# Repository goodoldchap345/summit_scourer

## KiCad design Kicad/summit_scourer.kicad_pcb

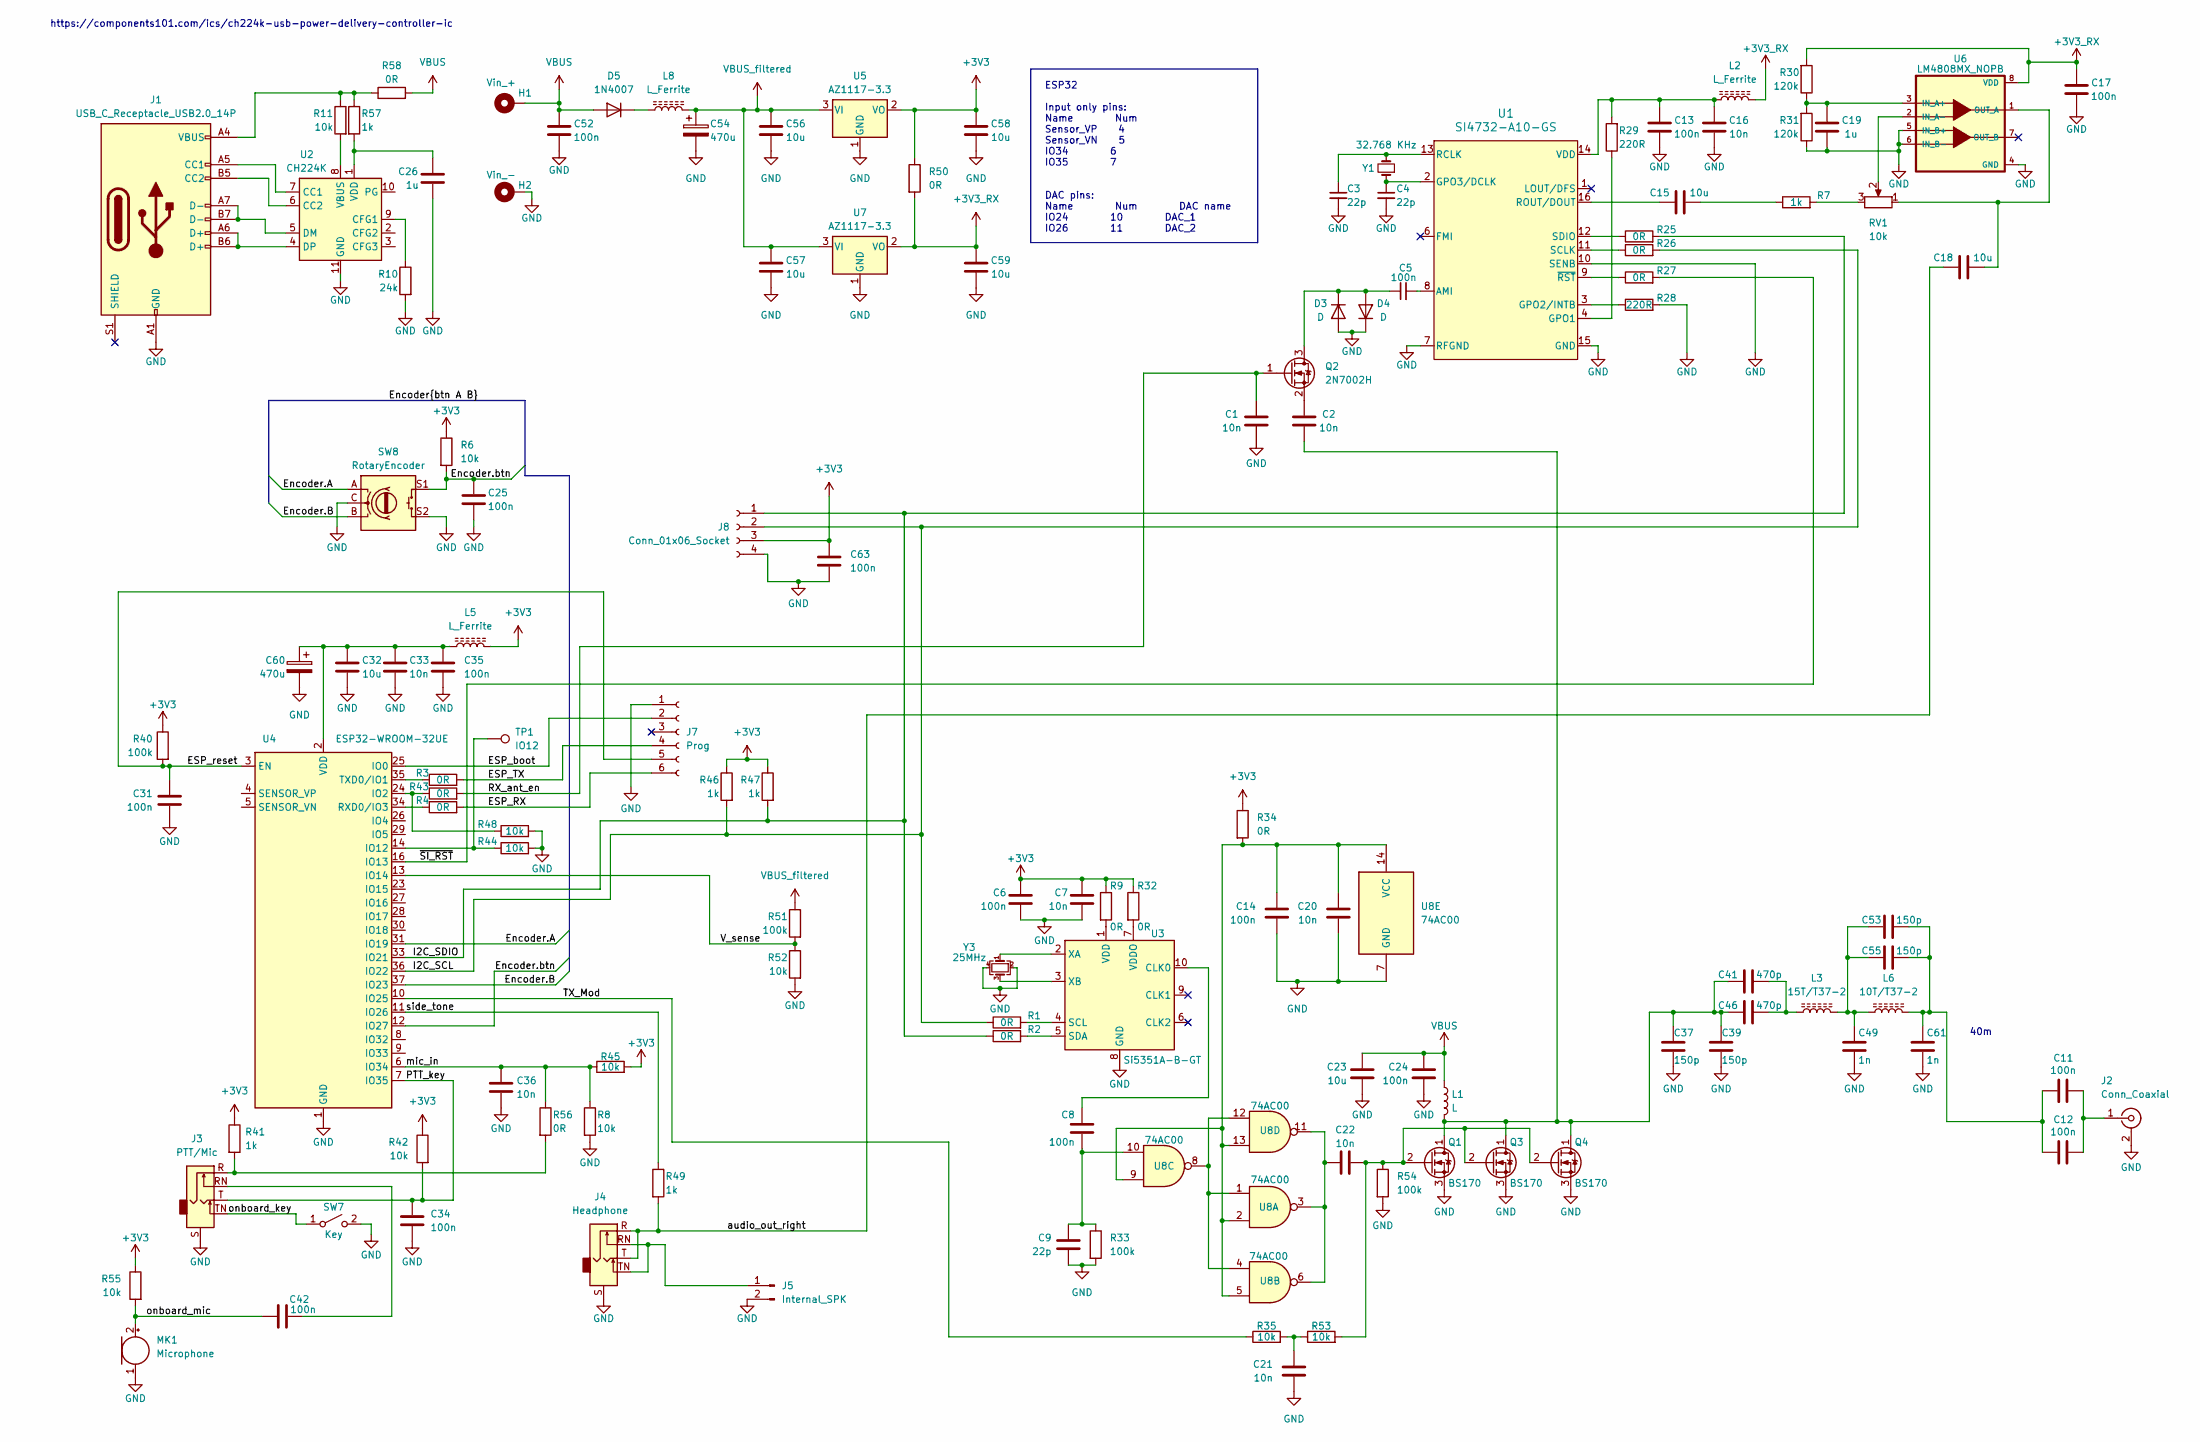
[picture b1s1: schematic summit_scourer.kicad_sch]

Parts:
C1, C2, C7, C16, C20, C21, C22, C33, C36: 10n; C_0603_1608Metric_Pad1.08x0.95mm_HandSolder
C3, C4, C9: 22p; C_0603_1608Metric_Pad1.08x0.95mm_HandSolder
C5, C6, C8, C11, C12, C13, C14, C17, C24, C25, C31, C34, C35, C42, C52, C63: 100n; C_0603_1608Metric_Pad1.08x0.95mm_HandSolder
C15, C18, C32, C56, C57, C58, C59: 10u; C_1210_3225Metric_Pad1.33x2.70mm_HandSolder
C19, C26: 1u; C_0603_1608Metric_Pad1.08x0.95mm_HandSolder
C23: 10u; C_1210_3225Metric
C37, C39, C53, C55: 150p; C_0603_1608Metric_Pad1.08x0.95mm_HandSolder
C41, C46: 470p; C_0603_1608Metric_Pad1.08x0.95mm_HandSolder
C49, C61: 1n; C_0603_1608Metric_Pad1.08x0.95mm_HandSolder
C54, C60: 470u; CP_Radial_D8.0mm_P3.80mm
D3, D4: D; D_PowerDI-123
D5: 1N4007; D_A-405_P2.54mm_Vertical_AnodeUp
H1: Vin_+; TestPoint_THTPad_3.0x3.0mm_Drill1.5mm
H2: Vin_-; TestPoint_THTPad_3.0x3.0mm_Drill1.5mm
J1: USB_C_Receptacle_USB2.0_14P; USB-C Korean_HROPart
J2: Conn_Coaxial; SMA_Amphenol_901-143_Horizontal
J3: PTT/Mic; Jack_3.5mm_CUI_SJ1-3525N_Horizontal
J4: Headphone; Jack_3.5mm_CUI_SJ1-3525N_Horizontal
J5: Internal_SPK; PinHeader_1x02_P2.54mm_Vertical
J7: Prog; PinHeader_1x06_P2.54mm_Vertical
J8: Conn_01x06_Socket; PinHeader_1x04_P2.54mm_Vertical
L1: L; L_Toroid_Vertical_L10.0mm_W5.0mm_P5.08mm
L2, L5: L_Ferrite; L_TDK_SLF6025
L3: 15T/T37-2; L_Toroid_Vertical_L10.0mm_W5.0mm_P5.08mm
L6: 10T/T37-2; L_Toroid_Vertical_L10.0mm_W5.0mm_P5.08mm
L8: L_Ferrite; L_6.3x6.3_H3
MK1: Microphone; PinHeader_1x02_P2.54mm_Vertical
Q1, Q3, Q4: BS170; TO-92_Inline
Q2: 2N7002H; SOT-23
R1, R2, R3, R4, R9, R25, R26, R27, R32, R34, R43, R50, R56, R58: 0R; R_0603_linked
R6, R8, R11, R35, R42, R44, R45, R48, R52, R53, R55: 10k; R_0603_1608Metric
R7, R41, R46, R47, R49, R57: 1k; R_0603_1608Metric
R10: 24k; R_0603_1608Metric
R28, R29: 220R; R_0603_1608Metric
R30, R31: 120k; R_0603_1608Metric
R33, R40, R51, R54: 100k; R_0603_1608Metric
RV1: 10k; PinHeader_1x03_P2.54mm_Vertical
SW7: Key; PinHeader_1x02_P2.54mm_Vertical
SW8: RotaryEncoder; Rotary_encoder
TP1: IO12; PinHeader_1x01_P2.54mm_Vertical
U1: SI4732-A10-GS; SO-16_3.9x9.9mm_P1.27mm
U2: CH224K; SSOP-10-1EP_3.9x4.9mm_P1mm_EP2.1x3.3mm
U3: Si5351A-B-GT; MSOP-10_3x3mm_P0.5mm
U4: ESP32-WROOM-32UE
U5, U7: AZ1117-3.3; TO-252-2
U6: LM4808MX_NOPB; SO-8_3.9x4.9mm_P1.27mm
U8: 74AC00; SOIC-14_3.9x8.7mm_P1.27mm
Y1: 32.768 KHz; Crystal_SMD_3215-2Pin_3.2x1.5mm; Part Num ABS07AIG-32.768KHZ-D-T
Y3: 25MHz; Crystal_SMD_3225-4Pin_3.2x2.5mm

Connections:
+3V3: C6.1, C7.1, C58.1, C63.1, J8.3, L5.2, R6.1, R9.1, R32.1, R34.1, R40.1, R41.1, R42.1, R45.2, R46.1, R47.1, R50.1, R55.1, U5.2 (VO)
+3V3_RX: C17.1, C59.1, L2.2, R30.2, R50.2, U6.8 (VDD), U7.2 (VO)
/ESP_RX: J7.6, R4.2
/ESP_TX: J7.4, R3.2
/ESP_boot: J7.2, U4.25 (IO0)
/ESP_reset: C31.1, J7.5, R40.2, U4.3 (EN)
/Encoder.A: SW8.A, U4.31 (IO19)
/Encoder.B: SW8.B, U4.37 (IO23)
/Encoder.btn: C25.1, R6.2, SW8.S1, U4.12 (IO27)
/I2C_SCL: J8.2, R1.1, R26.2, R46.2, U4.36 (IO22)
/I2C_SDIO: J8.1, R2.1, R25.2, R47.2, U4.33 (IO21)
/PTT_key: C34.1, J3.T, R42.2, U4.7 (IO35)
/RX_ant_en: C1.1, Q2.1 (G), R43.2
/TX_Mod: R35.1, U4.10 (IO25)
/V_sense: R51.2, R52.1, U4.13 (IO14)
/audio_out_right: C18.1, J4.R, J4.T, R49.2
/mic_in: C36.1, R8.1, R45.1, R56.1, U4.6 (IO34)
/onboard_key: J3.TN, SW7.1 (A)
/onboard_mic: C42.1, MK1.2 (+), R55.2
/side_tone: R49.1, U4.11 (IO26)
/~SI_RST: R27.2, U4.16 (IO13)
GND: C1.2, C3.2, C4.2, C6.2, C7.2, C9.2, C13.2, C14.2, C16.2, C17.2, C19.2, C20.2, C21.2, C23.2, C24.2, C25.2, C26.2, C31.2, C32.2, C33.2, C34.2, C35.2, C36.2, C37.2, C39.2, C49.1, C52.2, C54.2, C56.2, C57.2, C58.2, C59.2, C60.2, C61.2, C63.2, D3.2 (A), D4.1 (K), H2.1, J1.A1 (GND), J1.A12 (GND), J1.B1 (GND), J1.B12 (GND), J2.2 (Ext), J3.S, J4.S, J5.2, J7.1, J8.4, MK1.1 (-), Q1.3 (S), Q3.3 (S), Q4.3 (S), R8.2, R10.2, R28.2, R31.1, R33.2, R44.2, R48.2, R52.2, R54.2, SW7.2 (B), SW8.C, SW8.S2, U1.7 (RFGND), U1.10 (SENB), U1.15 (GND), U2.11 (GND), U3.8 (GND), U4.1 (GND), U4.15 (GND), U4.38 (GND), U4.39 (GND), U5.1 (GND), U6.4 (GND), U6.5 (IN_B+), U6.6 (IN_B-), U7.1 (GND), U8.7 (GND), Y3.2, Y3.4
unnamed: C8.1, C9.1, R33.1, U8.10
unnamed: C11.1, C12.1, C53.2, C55.2, C61.1, L6.2
unnamed: C15.2, R7.1
unnamed: C21.1, R35.2, R53.1
unnamed: C22.1, U8.3, U8.6, U8.11
unnamed: C41.2, C46.2, L3.1
unnamed: C42.2, J3.RN
unnamed: C49.2, C53.1, C55.1, L3.2, L6.1
unnamed: C5.1, D3.1 (K), D4.2 (A), Q2.3 (D)
unnamed: D5.1 (K), L8.1
unnamed: J1.A5 (CC1), U2.7 (CC1)
unnamed: J1.B5 (CC2), U2.6 (CC2)
unnamed: J1.A4 (VBUS), J1.A9 (VBUS), J1.B4 (VBUS), J1.B9 (VBUS), R11.1, R57.1, R58.1
unnamed: C11.2, C12.2, J2.1 (In)
unnamed: J3.R, R41.2, R56.2
unnamed: J4.RN, J4.TN, J5.1
unnamed: C2.2, C37.1, C39.1, C41.1, C46.1, L1.2, Q1.1 (D), Q3.1 (D), Q4.1 (D)
unnamed: C22.2, Q1.2 (G), Q3.2 (G), Q4.2 (G), R53.2, R54.1
unnamed: C2.1, Q2.2 (S)
unnamed: R7.2, RV1.3
unnamed: C5.2, U1.8 (AMI)
unnamed: R29.1, U1.4 (GPO1)
unnamed: R28.1, U1.3 (GPO2/INTB)
unnamed: C4.1, U1.2 (GPO3/DCLK), Y1.1
unnamed: C3.1, U1.13 (RCLK), Y1.2
unnamed: C15.1, U1.16 (ROUT/DOUT)
unnamed: R26.1, U1.11 (SCLK)
unnamed: R25.1, U1.12 (SDIO)
unnamed: C13.1, C16.1, L2.1, R29.2, U1.14 (VDD)
unnamed: R27.1, U1.9 (~RST)
unnamed: R10.1, U2.9 (CFG1)
unnamed: J1.A7 (D-), J1.B7 (D-), U2.5 (DM)
unnamed: J1.A6 (D+), J1.B6 (D+), U2.4 (DP)
unnamed: R11.2, U2.8 (VBUS)
unnamed: C26.1, R57.2, U2.1 (VDD)
unnamed: C8.2, U3.10 (CLK0)
unnamed: R1.2, U3.4 (SCL)
unnamed: R2.2, U3.5 (SDA)
unnamed: R9.2, U3.1 (VDD)
unnamed: R32.2, U3.7 (VDDO)
unnamed: U3.2 (XA), Y3.1
unnamed: U3.3 (XB), Y3.3
unnamed: R43.1, R48.1, U4.24 (IO2)
unnamed: R44.1, TP1.1, U4.14 (IO12)
unnamed: R4.1, U4.34 (RXD0/IO3)
unnamed: R3.1, U4.35 (TXD0/IO1)
unnamed: C32.1, C33.1, C35.1, C60.1, L5.1, U4.2 (VDD)
unnamed: C19.1, R30.1, R31.2, U6.3 (IN_A+)
unnamed: RV1.2, U6.2 (IN_A-)
unnamed: C18.2, RV1.1, U6.1 (OUT_A)
unnamed: U8.1, U8.4, U8.8, U8.12
unnamed: C14.1, C20.1, R34.2, U8.2, U8.5, U8.9, U8.13, U8.14 (VCC)
VBUS: C23.1, C24.1, C52.1, D5.2 (A), H1.1, L1.1, R58.2
VBUS_filtered: C54.1, C56.1, C57.1, L8.2, R51.1, U5.3 (VI), U7.3 (VI)

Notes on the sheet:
ESP32 Input only pins: Name Num Sensor_VP 4 Sensor_VN 5 IO34 6 IO35 7 DAC pins: Name Num DAC name IO24 10 DAC_1 IO26 11 DAC_2
https://components101.com/ics/ch224k-usb-power-delivery-controller-ic
40m

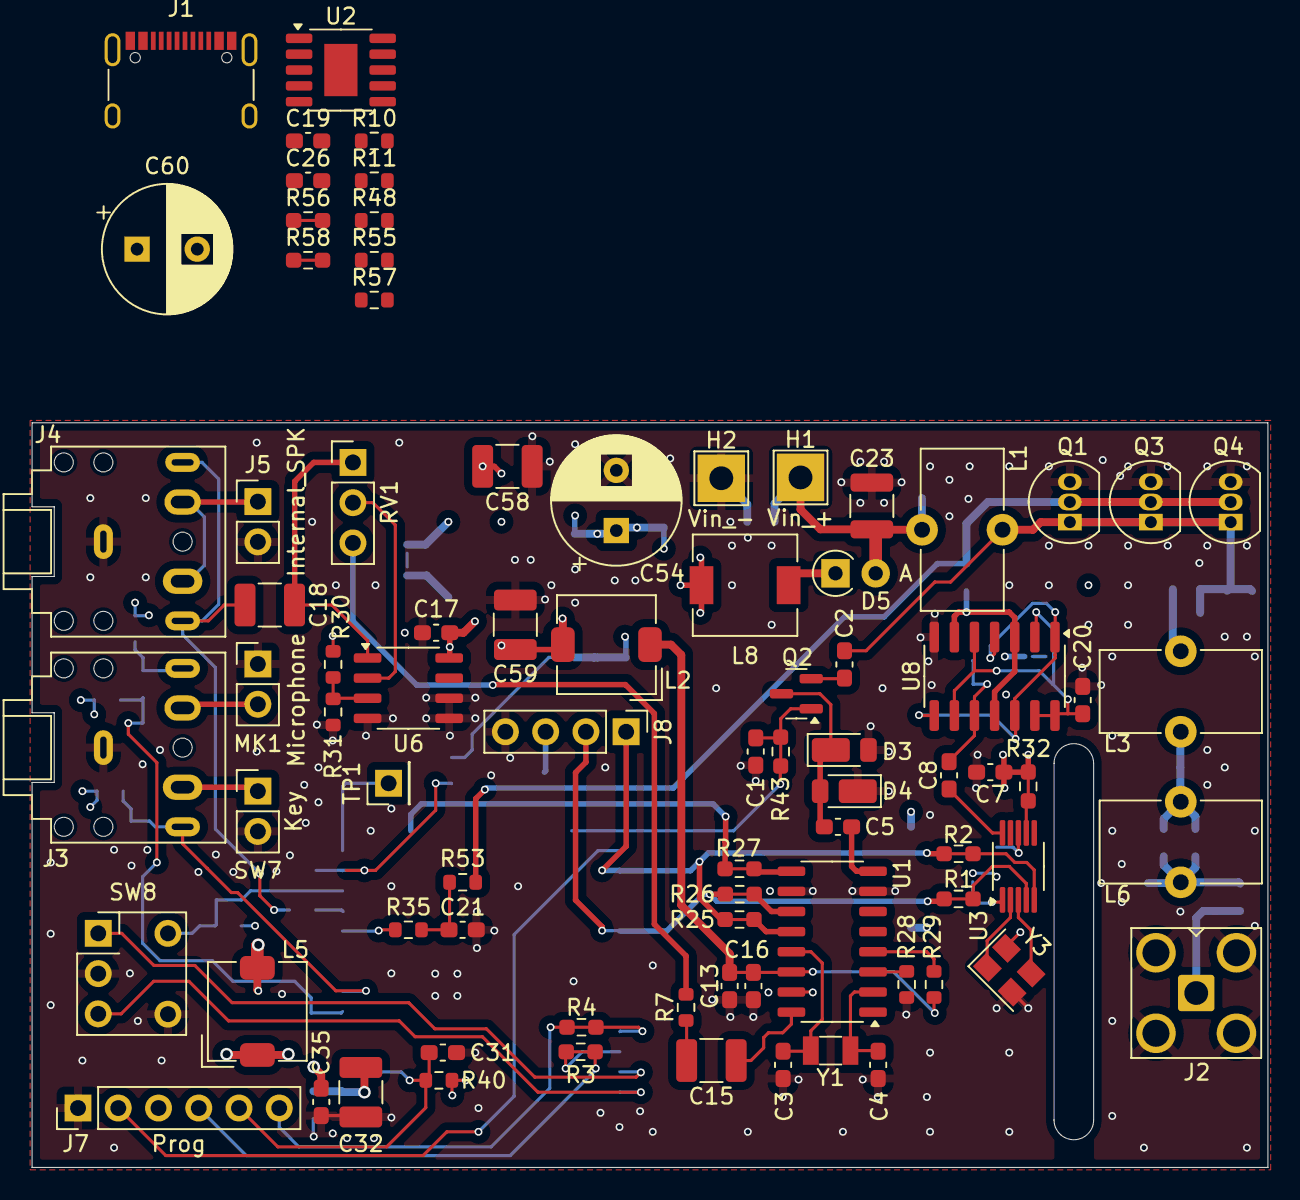
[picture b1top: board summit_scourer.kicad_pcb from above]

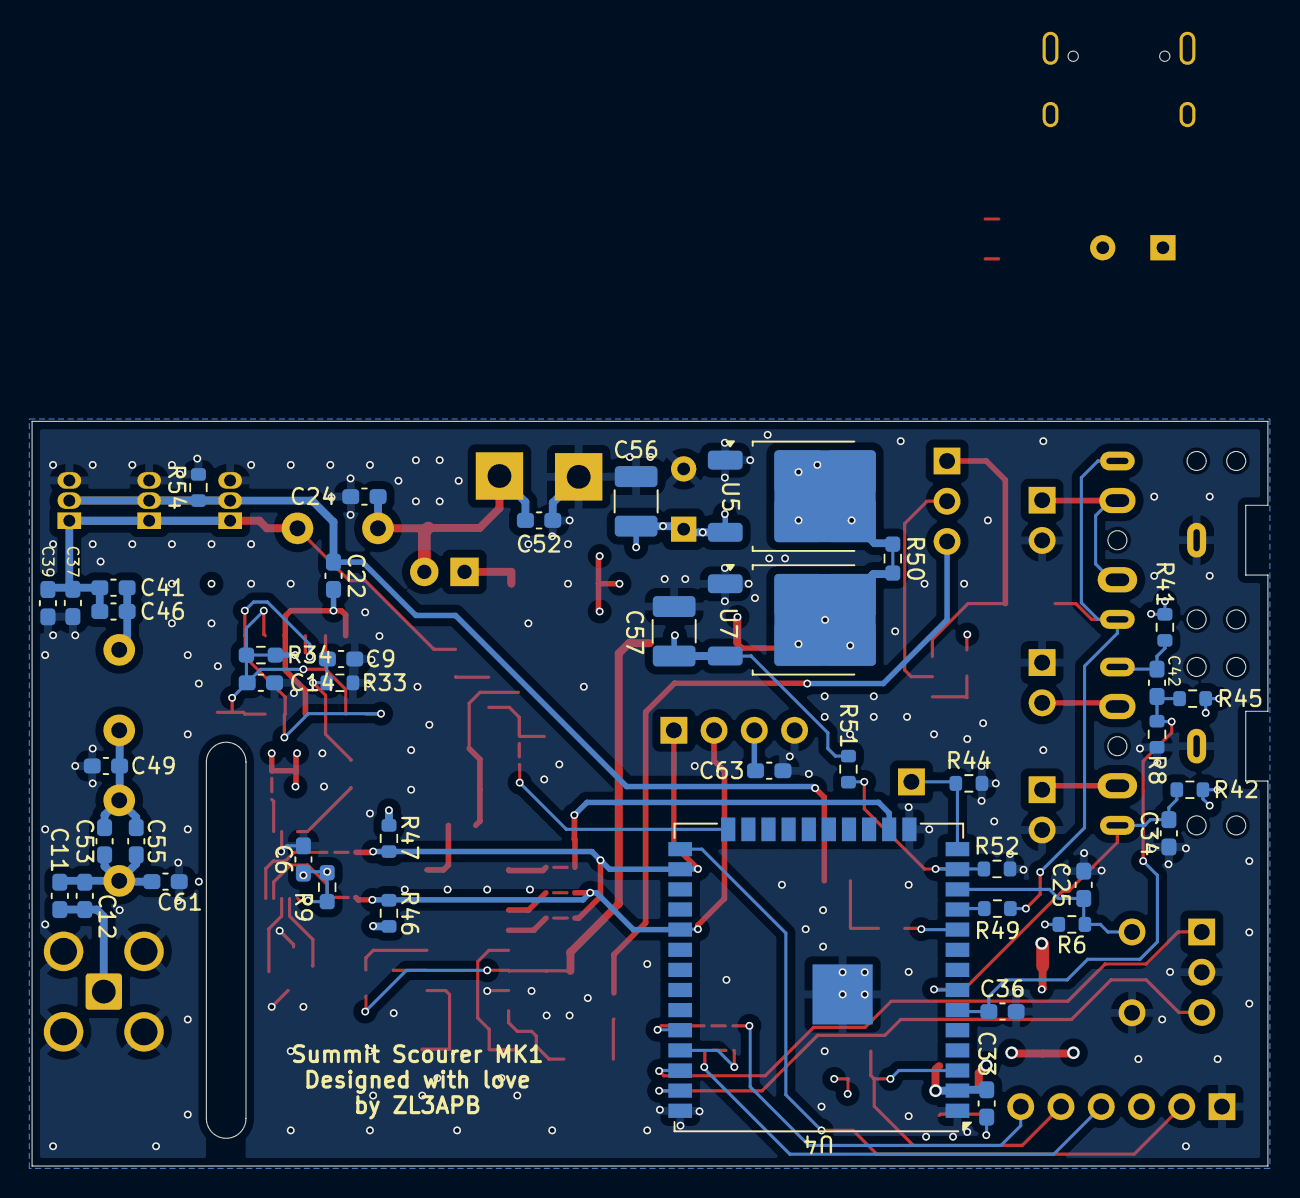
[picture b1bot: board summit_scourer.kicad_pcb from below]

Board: 4 copper layers, 78.0 x 47.0 mm, 125 parts (43 on the bottom side), 76 nets.

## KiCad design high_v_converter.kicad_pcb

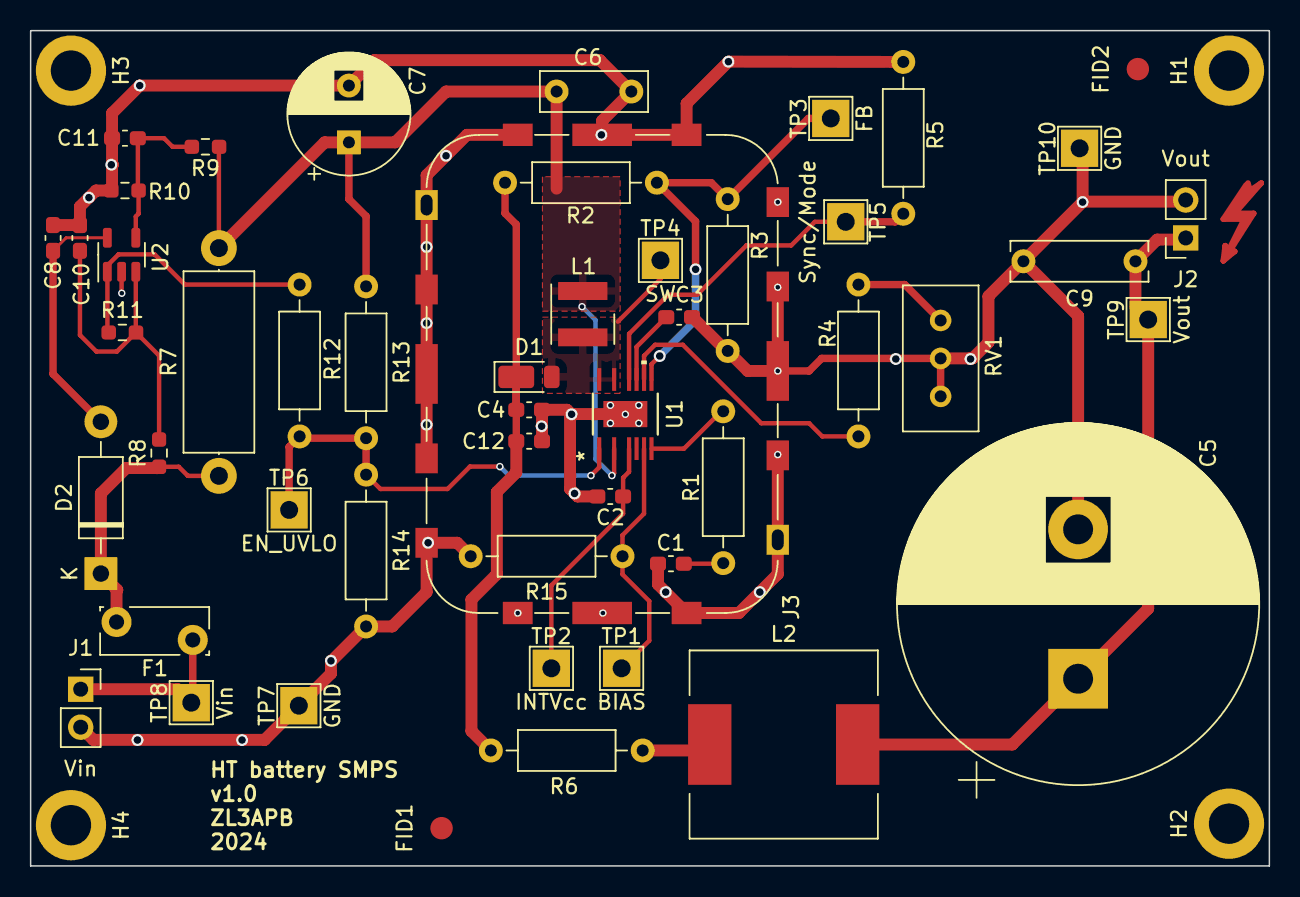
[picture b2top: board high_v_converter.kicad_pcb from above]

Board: 2 copper layers, 82.9 x 55.9 mm, 55 parts (0 on the bottom side), 22 nets.

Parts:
C1: 1n; C_0603_1608Metric_Pad1.08x0.95mm_HandSolder
C2: 1u; C_0603_1608Metric_Pad1.08x0.95mm_HandSolder
C3: 220n; C_0603_1608Metric_Pad1.08x0.95mm_HandSolder
C4, C8, C10, C11, C12: 100n; C_0603_1608Metric_Pad1.08x0.95mm_HandSolder
C5: 150u; CP_Radial_D24.0mm_P10.00mm_SnapIn
C6: 100n; C_Disc_D7.0mm_W2.5mm_P5.00mm
C7: 120u; CP_Radial_D8.0mm_P3.80mm
C9: 100n; C_Rect_L9.0mm_W2.5mm_P7.50mm_MKT
D1: D; D_PowerDI-123
D2: 3v3; D_DO-41_SOD81_P10.16mm_Horizontal
F1: 3A; Fuse_Bourns_MF-RG300
FID1, FID2: Fiducial; Fiducial_1.5mm_Mask3mm
H1, H2, H3, H4: MountingHole_Pad; MountingHole_2.7mm_M2.5_DIN965_Pad
J1: Vin; PinSocket_1x02_P2.54mm_Vertical
J2: Vout; PinSocket_1x02_P2.54mm_Vertical
J3: RF_Shield_PSU; MS323_hatched
L1: 10u; L_Wurth_WE-LQSH-4020
L2: 22uH, 80.4mOhm; L_12x12mm_H8mm
R1: 84k5; R_Axial_DIN0207_L6.3mm_D2.5mm_P10.16mm_Horizontal
R2: 1M; R_Axial_DIN0207_L6.3mm_D2.5mm_P10.16mm_Horizontal
R3: 12k7; R_Axial_DIN0207_L6.3mm_D2.5mm_P10.16mm_Horizontal
R4: 47k; R_Axial_DIN0207_L6.3mm_D2.5mm_P10.16mm_Horizontal
R5, R12, R13, R15: 0R; R_Axial_DIN0207_L6.3mm_D2.5mm_P10.16mm_Horizontal
R6: 10R; R_Axial_DIN0207_L6.3mm_D2.5mm_P10.16mm_Horizontal
R7: 1R; R_Axial_DIN0414_L11.9mm_D4.5mm_P15.24mm_Horizontal
R8, R9: 10k; R_0603_1608Metric_Pad0.98x0.95mm_HandSolder
R10, R11: 1M; R_0603_1608Metric_Pad0.98x0.95mm_HandSolder
R14: 100k; R_Axial_DIN0207_L6.3mm_D2.5mm_P10.16mm_Horizontal
RV1: 500k; Potentiometer_Bourns_3296W_Vertical
SYM1: SYM_Flash_XLarge; Symbol_Highvoltage_Type1_CopperTop_Small
TP1: BIAS; TestPoint_THTPad_2.5x2.5mm_Drill1.2mm
TP2: INTVcc; TestPoint_THTPad_2.5x2.5mm_Drill1.2mm
TP3: FB; TestPoint_THTPad_2.5x2.5mm_Drill1.2mm
TP4: SW; TestPoint_THTPad_2.5x2.5mm_Drill1.2mm
TP5: Sync/Mode; TestPoint_THTPad_2.5x2.5mm_Drill1.2mm
TP6: EN_UVLO; TestPoint_THTPad_2.5x2.5mm_Drill1.2mm
TP7, TP10: GND; TestPoint_THTPad_2.5x2.5mm_Drill1.2mm
TP8: Vin; TestPoint_THTPad_2.5x2.5mm_Drill1.2mm
TP9: Vout; TestPoint_THTPad_2.5x2.5mm_Drill1.2mm
U1: LT8365JMSE-PBF; 05-08-1871_ADI-M
U2: MCP6001T-I/OT; SOT-23-5

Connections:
GND: C1.2, C2.2, C3.2, C4.2, C5.2, C6.2, C7.2, C8.2, C9.2, C10.2, C11.2, C12.2, H1.1, H2.1, H3.1, H4.1, J1.2, J2.2, J3.1 (Shield), R3.2, R5.2, R10.2, R14.2, R15.2, RV1.2, RV1.3, TP7.1, TP10.1, U1.17 (PGND/GND), U2.2 (V-)
unnamed: C1.1, R1.2
unnamed: D1.2 (A), L1.2, TP4.1, U1.14 (SW2), U1.16 (SW1)
unnamed: C4.1, C12.1, D1.1 (K), R2.1, R6.1
unnamed: C8.1, D2.2 (A), U2.5 (V+)
unnamed: D2.1 (K), F1.2, R7.1, R8.1
unnamed: F1.1, J1.1, TP8.1
unnamed: C5.1, C9.1, J2.1, L2.2, TP9.1
unnamed: L2.1, R6.2
unnamed: R4.2, RV1.1
unnamed: R11.2, R12.1, U2.1
unnamed: R15.1, TP1.1, U1.7 (BIAS)
unnamed: R12.2, R13.2, R14.1, TP6.1, U1.1 (EN/UVLO)
unnamed: R2.2, R3.1, TP3.1, U1.9 (FBX)
unnamed: C2.1, TP2.1, U1.5 (INTVCC)
unnamed: R4.1, U1.10 (RT)
unnamed: C3.1, U1.11 (SS)
unnamed: R5.1, TP5.1, U1.12 (SYNC/MODE)
unnamed: R1.1, U1.8 (VC)
unnamed: C6.1, C7.1, L1.1, R7.2, R9.1, R13.1, U1.3 (VIN)
unnamed: C10.1, R8.2, R11.1, U2.3 (+)
unnamed: C11.1, R9.2, R10.1, U2.4 (-)

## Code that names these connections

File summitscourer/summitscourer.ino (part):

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#define LSB 1
#define USB 2
#define AM_FUNCTION 1
#define RX_ANT_EN 2

//Scheduler
#define MILLIS_PER_DISPLAY_UPDATE 1000
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#include <analogWrite.h>
#include "soc/rtc_wdt.h"
#define I2C_SDA 21
#define I2C_SCL 22
#define AD_ADDR 0x60
#define SIDETONE_FREQUENCY 800

// TX other
#define PTT_KEY 35
#define SIDETONE_PIN 26
#define DAC_CH1 25
#define DAC_CH2 26
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
  pinMode(ENCODER_BUTTON, INPUT_PULLUP);
  pinMode(ENCODER_BUTTON, INPUT);
  pinMode(RX_ANT_EN, OUTPUT);
  digitalWrite(RX_ANT_EN, HIGH);

  pinMode(PTT_KEY, INPUT);
  pinMode(DAC_CH1, OUTPUT);
  digitalWrite(DAC_CH1, 0);

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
